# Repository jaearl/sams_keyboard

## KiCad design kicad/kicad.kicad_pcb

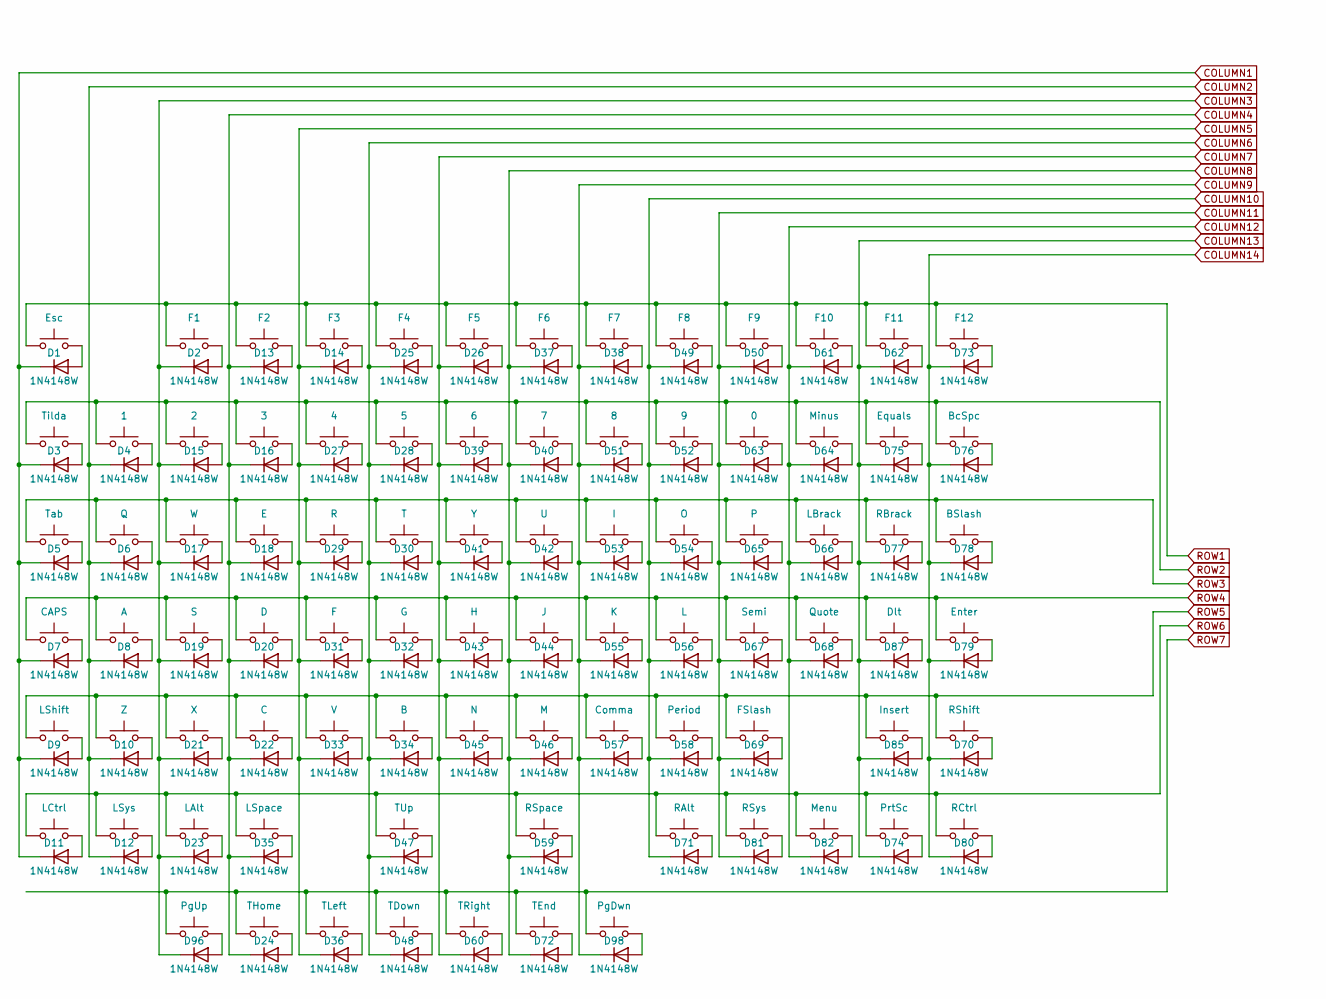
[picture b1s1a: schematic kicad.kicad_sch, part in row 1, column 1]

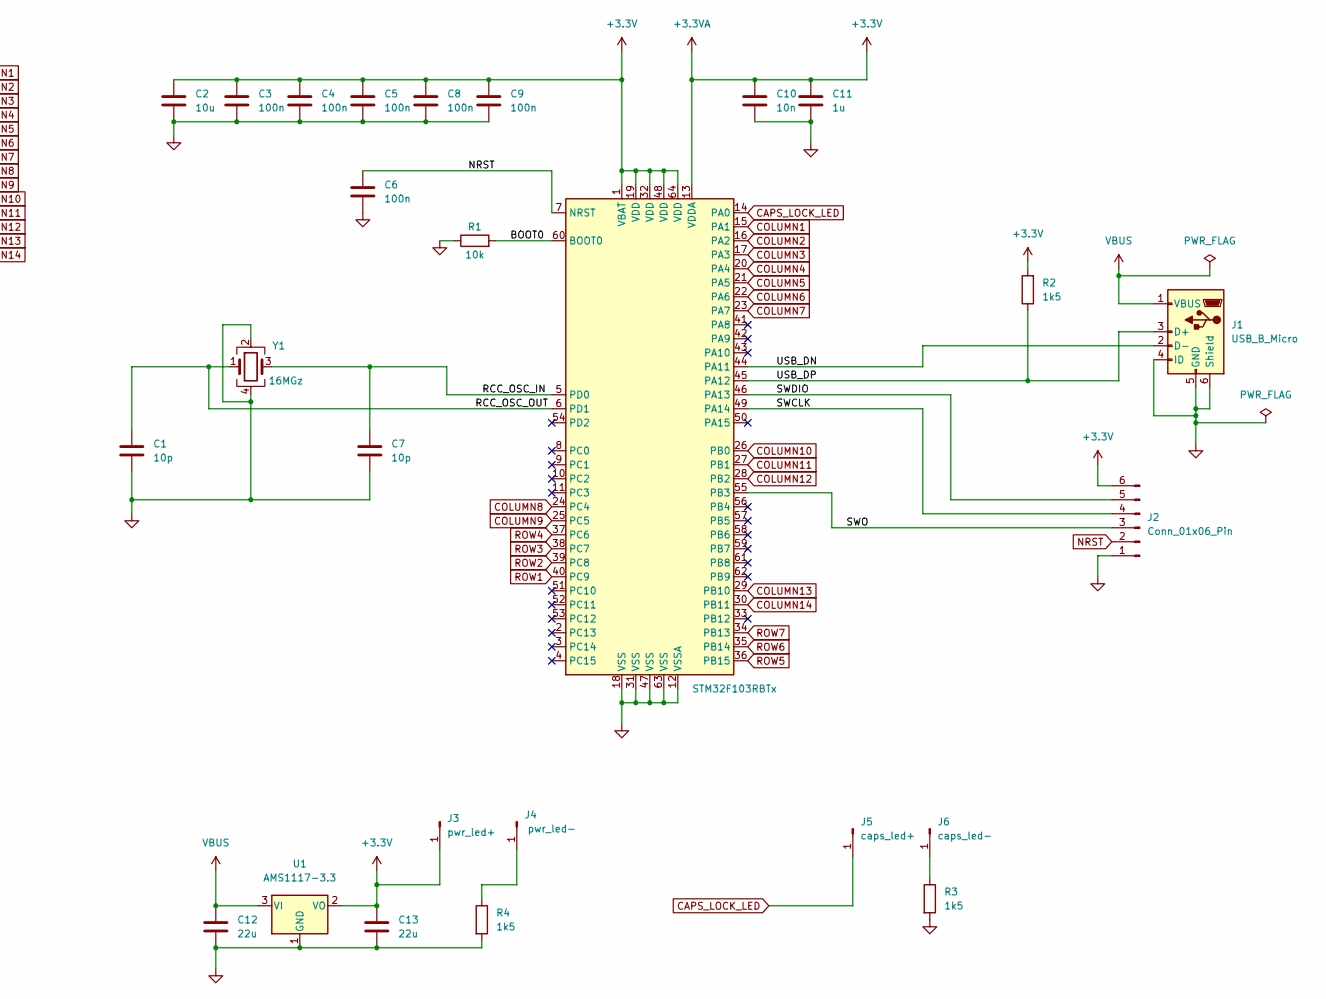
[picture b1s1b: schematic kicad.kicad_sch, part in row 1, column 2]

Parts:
C1, C7: 10p; C_0402_1005Metric
C2: 10u; C_0603_1608Metric
C3, C4, C5, C6, C8, C9: 100n; C_0402_1005Metric
C10: 10n; C_0402_1005Metric
C11: 1u; C_0402_1005Metric
C12, C13: 22u; C_0805_2012Metric
D1, D2, D3, D4, D5, D6, D7, D8, D9, D10, D11, D12, D13, D14, D15, D16, D17, D18, D19, D20, D21, D22, D23, D24, D25, D26, D27, D28, D29, D30, D31, D32, D33, D34, D35, D36, D37, D38, D39, D40, D41, D42, D43, D44, D45, D46, D47, D48, D49, D50, D51, D52, D53, D54, D55, D56, D57, D58, D59, D60, D61, D62, D63, D64, D65, D66, D67, D68, D69, D70, D71, D72, D73, D74, D75, D76, D77, D78, D79, D80, D81, D82, D85, D87, D96, D98: 1N4148W; D_SOD-123
J1: USB_B_Micro; USB_Micro-B_Wuerth_629105150521
J2: Conn_01x06_Pin
J3: pwr_led+; PinHeader_1x01_P2.54mm_Vertical
J4: pwr_led-; PinHeader_1x01_P2.54mm_Vertical
J5: caps_led+; PinHeader_1x01_P2.54mm_Vertical
J6: caps_led-; PinHeader_1x01_P2.54mm_Vertical
MCU1: STM32F103RBTx; LQFP-64_10x10mm_P0.5mm
R1: 10k; R_0402_1005Metric
R2: 1k5; R_0402_1005Metric
R3, R4: 1k5; R_0603_1608Metric
U1: AMS1117-3.3; SOT-223-3_TabPin2
Y1: 16MGz; Crystal_SMD_3225-4Pin_3.2x2.5mm
sw1: Esc; SW_Cherry_MX_1.00u_PCB
sw2: F1; SW_Cherry_MX_1.00u_PCB
sw3: Tilda; SW_Cherry_MX_1.00u_PCB
sw4: 1; SW_Cherry_MX_1.00u_PCB
sw5: Tab; SW_Cherry_MX_1.50u_PCB
sw6: Q; SW_Cherry_MX_1.00u_PCB
sw7: CAPS; SW_Cherry_MX_1.75u_PCB
sw8: A; SW_Cherry_MX_1.00u_PCB
sw9: LShift; SW_Cherry_MX_2.25u_PCB
sw10: Z; SW_Cherry_MX_1.00u_PCB
sw11: LCtrl; SW_Cherry_MX_1.25u_PCB
sw12: LSys; SW_Cherry_MX_1.25u_PCB
sw13: F2; SW_Cherry_MX_1.00u_PCB
sw14: F3; SW_Cherry_MX_1.00u_PCB
sw15: 2; SW_Cherry_MX_1.00u_PCB
sw16: 3; SW_Cherry_MX_1.00u_PCB
sw17: W; SW_Cherry_MX_1.00u_PCB
sw18: E; SW_Cherry_MX_1.00u_PCB
sw19: S; SW_Cherry_MX_1.00u_PCB
sw20: D; SW_Cherry_MX_1.00u_PCB
sw21: X; SW_Cherry_MX_1.00u_PCB
sw22: C; SW_Cherry_MX_1.00u_PCB
sw23: LAlt; SW_Cherry_MX_1.25u_PCB
sw24: THome; SW_Cherry_MX_1.00u_PCB
sw25: F4; SW_Cherry_MX_1.00u_PCB
sw26: F5; SW_Cherry_MX_1.00u_PCB
sw27: 4; SW_Cherry_MX_1.00u_PCB
sw28: 5; SW_Cherry_MX_1.00u_PCB
sw29: R; SW_Cherry_MX_1.00u_PCB
sw30: T; SW_Cherry_MX_1.00u_PCB
sw31: F; SW_Cherry_MX_1.00u_PCB
sw32: G; SW_Cherry_MX_1.00u_PCB
sw33: V; SW_Cherry_MX_1.00u_PCB
sw34: B; SW_Cherry_MX_1.00u_PCB
sw35: LSpace; SW_Cherry_MX_2.75u_PCB
sw36: TLeft; SW_Cherry_MX_1.00u_PCB
sw37: F6; SW_Cherry_MX_1.00u_PCB
sw38: F7; SW_Cherry_MX_1.00u_PCB
sw39: 6; SW_Cherry_MX_1.00u_PCB
sw40: 7; SW_Cherry_MX_1.00u_PCB
sw41: Y; SW_Cherry_MX_1.00u_PCB
sw42: U; SW_Cherry_MX_1.00u_PCB
sw43: H; SW_Cherry_MX_1.00u_PCB
sw44: J; SW_Cherry_MX_1.00u_PCB
sw45: N; SW_Cherry_MX_1.00u_PCB
sw46: M; SW_Cherry_MX_1.00u_PCB
sw47: TUp; SW_Cherry_MX_1.00u_PCB
sw48: TDown; SW_Cherry_MX_1.00u_PCB
sw49: F8; SW_Cherry_MX_1.00u_PCB
sw50: F9; SW_Cherry_MX_1.00u_PCB
sw51: 8; SW_Cherry_MX_1.00u_PCB
sw52: 9; SW_Cherry_MX_1.00u_PCB
sw53: I; SW_Cherry_MX_1.00u_PCB
sw54: O; SW_Cherry_MX_1.00u_PCB
sw55: K; SW_Cherry_MX_1.00u_PCB
sw56: L; SW_Cherry_MX_1.00u_PCB
sw57: Comma; SW_Cherry_MX_1.00u_PCB
sw58: Period; SW_Cherry_MX_1.00u_PCB
sw59: RSpace; SW_Cherry_MX_2.25u_PCB
sw60: TRight; SW_Cherry_MX_1.00u_PCB
sw61: F10; SW_Cherry_MX_1.00u_PCB
sw62: F11; SW_Cherry_MX_1.00u_PCB
sw63: 0; SW_Cherry_MX_1.00u_PCB
sw64: Minus; SW_Cherry_MX_1.00u_PCB
sw65: P; SW_Cherry_MX_1.00u_PCB
sw66: LBrack; SW_Cherry_MX_1.00u_PCB
sw67: Semi; SW_Cherry_MX_1.00u_PCB
sw68: Quote; SW_Cherry_MX_1.00u_PCB
sw69: FSlash; SW_Cherry_MX_1.00u_PCB
sw70: RShift; SW_Cherry_MX_2.75u_PCB
sw71: RAlt; SW_Cherry_MX_1.25u_PCB
sw72: TEnd; SW_Cherry_MX_1.00u_PCB
sw73: F12; SW_Cherry_MX_1.00u_PCB
sw74: PrtSc; SW_Cherry_MX_1.00u_PCB
sw75: Equals; SW_Cherry_MX_1.00u_PCB
sw76: BcSpc; SW_Cherry_MX_2.00u_PCB
sw77: RBrack; SW_Cherry_MX_1.00u_PCB
sw78: BSlash; SW_Cherry_MX_1.50u_PCB
sw79: Enter; SW_Cherry_MX_2.25u_PCB
sw80: RCtrl; SW_Cherry_MX_1.25u_PCB
sw81: RSys; SW_Cherry_MX_1.25u_PCB
sw82: Menu; SW_Cherry_MX_1.25u_PCB
sw85: Insert; SW_Cherry_MX_1.00u_PCB
sw87: Dlt; SW_Cherry_MX_1.00u_PCB
sw96: PgUp; SW_Cherry_MX_1.00u_PCB
sw98: PgDwn; SW_Cherry_MX_1.00u_PCB

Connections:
/BOOT0: MCU1.60 (BOOT0), R1.2
/RCC_OSC_IN: C7.1, MCU1.5 (PD0), Y1.3
/RCC_OSC_OUT: C1.1, MCU1.6 (PD1), Y1.1
/USB_DN: J1.2 (D-), MCU1.44 (PA11)
/USB_DP: J1.3 (D+), MCU1.45 (PA12), R2.1
CAPS_LOCK_LED: J5.1, MCU1.14 (PA0)
COLUMN1: D1.1 (K), D3.1 (K), D5.1 (K), D7.1 (K), D9.1 (K), D11.1 (K), MCU1.15 (PA1)
COLUMN2: D4.1 (K), D6.1 (K), D8.1 (K), D10.1 (K), D12.1 (K), MCU1.16 (PA2)
COLUMN3: D2.1 (K), D15.1 (K), D17.1 (K), D19.1 (K), D21.1 (K), D23.1 (K), D96.1 (K), MCU1.17 (PA3)
COLUMN4: D13.1 (K), D16.1 (K), D18.1 (K), D20.1 (K), D22.1 (K), D24.1 (K), D35.1 (K), MCU1.20 (PA4)
COLUMN5: D14.1 (K), D27.1 (K), D29.1 (K), D31.1 (K), D33.1 (K), D36.1 (K), MCU1.21 (PA5)
COLUMN6: D25.1 (K), D28.1 (K), D30.1 (K), D32.1 (K), D34.1 (K), D47.1 (K), D48.1 (K), MCU1.22 (PA6)
COLUMN7: D26.1 (K), D39.1 (K), D41.1 (K), D43.1 (K), D45.1 (K), D60.1 (K), MCU1.23 (PA7)
COLUMN8: D37.1 (K), D40.1 (K), D42.1 (K), D44.1 (K), D46.1 (K), D59.1 (K), D72.1 (K), MCU1.24 (PC4)
COLUMN9: D38.1 (K), D51.1 (K), D53.1 (K), D55.1 (K), D57.1 (K), D98.1 (K), MCU1.25 (PC5)
COLUMN10: D49.1 (K), D52.1 (K), D54.1 (K), D56.1 (K), D58.1 (K), D71.1 (K), MCU1.26 (PB0)
COLUMN11: D50.1 (K), D63.1 (K), D65.1 (K), D67.1 (K), D69.1 (K), D81.1 (K), MCU1.27 (PB1)
COLUMN12: D61.1 (K), D64.1 (K), D66.1 (K), D68.1 (K), D82.1 (K), MCU1.28 (PB2)
COLUMN13: D62.1 (K), D74.1 (K), D75.1 (K), D77.1 (K), D85.1 (K), D87.1 (K), MCU1.29 (PB10)
COLUMN14: D70.1 (K), D73.1 (K), D76.1 (K), D78.1 (K), D79.1 (K), D80.1 (K), MCU1.30 (PB11)
NRST: C6.1, MCU1.7 (NRST)
unnamed: D1.2 (A), sw1.2
unnamed: D2.2 (A), sw2.2
unnamed: D3.2 (A), sw3.2
unnamed: D4.2 (A), sw4.2
unnamed: D5.2 (A), sw5.2
unnamed: D6.2 (A), sw6.2
unnamed: D7.2 (A), sw7.2
unnamed: D8.2 (A), sw8.2
unnamed: D9.2 (A), sw9.2
unnamed: D10.2 (A), sw10.2
unnamed: D11.2 (A), sw11.2
unnamed: D12.2 (A), sw12.2
unnamed: D13.2 (A), sw13.2
unnamed: D14.2 (A), sw14.2
unnamed: D15.2 (A), sw15.2
unnamed: D16.2 (A), sw16.2
unnamed: D17.2 (A), sw17.2
unnamed: D18.2 (A), sw18.2
unnamed: D19.2 (A), sw19.2
unnamed: D20.2 (A), sw20.2
unnamed: D21.2 (A), sw21.2
unnamed: D22.2 (A), sw22.2
unnamed: D23.2 (A), sw23.2
unnamed: D24.2 (A), sw24.2
unnamed: D25.2 (A), sw25.2
unnamed: D26.2 (A), sw26.2
unnamed: D27.2 (A), sw27.2
unnamed: D28.2 (A), sw28.2
unnamed: D29.2 (A), sw29.2
unnamed: D30.2 (A), sw30.2
unnamed: D31.2 (A), sw31.2
unnamed: D32.2 (A), sw32.2
unnamed: D33.2 (A), sw33.2
unnamed: D34.2 (A), sw34.2
unnamed: D35.2 (A), sw35.2
unnamed: D36.2 (A), sw36.2
unnamed: D37.2 (A), sw37.2
unnamed: D38.2 (A), sw38.2
unnamed: D39.2 (A), sw39.2
unnamed: D40.2 (A), sw40.2
unnamed: D41.2 (A), sw41.2
unnamed: D42.2 (A), sw42.2
unnamed: D43.2 (A), sw43.2
unnamed: D44.2 (A), sw44.2
unnamed: D45.2 (A), sw45.2
unnamed: D46.2 (A), sw46.2
unnamed: D47.2 (A), sw47.2
unnamed: D48.2 (A), sw48.2
unnamed: D49.2 (A), sw49.2
unnamed: D50.2 (A), sw50.2
unnamed: D51.2 (A), sw51.2
unnamed: D52.2 (A), sw52.2
unnamed: D53.2 (A), sw53.2
unnamed: D54.2 (A), sw54.2
unnamed: D55.2 (A), sw55.2
unnamed: D56.2 (A), sw56.2
unnamed: D57.2 (A), sw57.2
unnamed: D58.2 (A), sw58.2
unnamed: D59.2 (A), sw59.2
unnamed: D60.2 (A), sw60.2
unnamed: D61.2 (A), sw61.2
unnamed: D62.2 (A), sw62.2
unnamed: D63.2 (A), sw63.2
unnamed: D64.2 (A), sw64.2
unnamed: D65.2 (A), sw65.2
unnamed: D66.2 (A), sw66.2
unnamed: D67.2 (A), sw67.2
unnamed: D68.2 (A), sw68.2
unnamed: D69.2 (A), sw69.2
unnamed: D70.2 (A), sw70.2
unnamed: D71.2 (A), sw71.2
unnamed: D72.2 (A), sw72.2
unnamed: D73.2 (A), sw73.2
unnamed: D74.2 (A), sw74.2
unnamed: D75.2 (A), sw75.2
unnamed: D76.2 (A), sw76.2
unnamed: D77.2 (A), sw77.2
unnamed: D78.2 (A), sw78.2
unnamed: D79.2 (A), sw79.2
unnamed: D80.2 (A), sw80.2
unnamed: D81.2 (A), sw81.2
unnamed: D82.2 (A), sw82.2
unnamed: D85.2 (A), sw85.2
unnamed: D87.2 (A), sw87.2
unnamed: D96.2 (A), sw96.2
unnamed: D98.2 (A), sw98.2
unnamed: J4.1, R4.1
unnamed: J6.1, R3.1
ROW1: MCU1.40 (PC9), sw1.1, sw2.1, sw13.1, sw14.1, sw25.1, sw26.1, sw37.1, sw38.1, sw49.1, sw50.1, sw61.1, sw62.1, sw73.1
ROW2: MCU1.39 (PC8), sw3.1, sw4.1, sw15.1, sw16.1, sw27.1, sw28.1, sw39.1, sw40.1, sw51.1, sw52.1, sw63.1, sw64.1, sw75.1, sw76.1
ROW3: MCU1.38 (PC7), sw5.1, sw6.1, sw17.1, sw18.1, sw29.1, sw30.1, sw41.1, sw42.1, sw53.1, sw54.1, sw65.1, sw66.1, sw77.1, sw78.1
ROW4: MCU1.37 (PC6), sw7.1, sw8.1, sw19.1, sw20.1, sw31.1, sw32.1, sw43.1, sw44.1, sw55.1, sw56.1, sw67.1, sw68.1, sw79.1, sw87.1
ROW5: MCU1.36 (PB15), sw9.1, sw10.1, sw21.1, sw22.1, sw33.1, sw34.1, sw45.1, sw46.1, sw57.1, sw58.1, sw69.1, sw70.1, sw85.1
ROW6: MCU1.35 (PB14), sw11.1, sw12.1, sw23.1, sw35.1, sw47.1, sw59.1, sw71.1, sw74.1, sw80.1, sw81.1, sw82.1
ROW7: MCU1.34 (PB13), sw24.1, sw36.1, sw48.1, sw60.1, sw72.1, sw96.1, sw98.1
VBUS: C12.1, J1.1 (VBUS), U1.3 (VI)

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
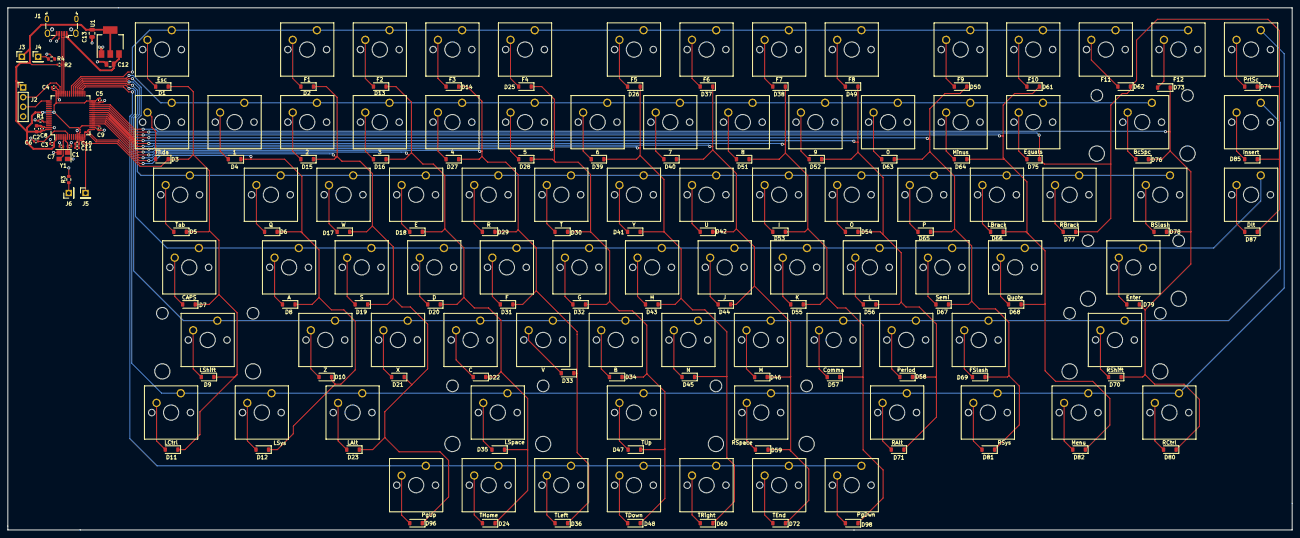
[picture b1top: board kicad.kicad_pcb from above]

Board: 2 copper layers, 337.0 x 137.0 mm, 198 parts (0 on the bottom side), 121 nets.

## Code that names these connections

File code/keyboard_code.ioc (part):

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Mcu.Name=STM32F103R(8-B)Tx
Mcu.Package=LQFP64
Mcu.UserName=STM32F103RBTx
PA0-WKUP.GPIOParameters=GPIO_PuPd,GPIO_Label
PA0-WKUP.GPIO_Label=COLUMN10
PA0-WKUP.GPIO_PuPd=GPIO_PULLDOWN
PA0-WKUP.Signal=GPIO_Input
PA13.Mode=Trace_Asynchronous_SW
PA13.Signal=SYS_JTMS-SWDIO
PA14.Mode=Trace_Asynchronous_SW
PA14.Signal=SYS_JTCK-SWCLK
PA6.GPIOParameters=GPIO_Speed,PinState,GPIO_PuPd,GPIO_Label
PA6.GPIO_Label=ROW7
PA6.GPIO_PuPd=GPIO_PULLDOWN
PA6.GPIO_Speed=GPIO_SPEED_FREQ_HIGH
PA6.PinState=GPIO_PIN_SET
PA6.Signal=GPIO_Output
PB0.GPIOParameters=GPIO_Speed,PinState,GPIO_PuPd,GPIO_Label,GPIO_ModeDefaultOutputPP
PB0.GPIO_Label=CAPS_LOCK
PB0.GPIO_ModeDefaultOutputPP=GPIO_MODE_OUTPUT_PP
PB0.GPIO_PuPd=GPIO_PULLDOWN
PB0.GPIO_Speed=GPIO_SPEED_FREQ_HIGH
PB0.PinState=GPIO_PIN_SET
PB0.Signal=GPIO_Output
PB3.Mode=Trace_Asynchronous_SW
PB3.Signal=SYS_JTDO-TRACESWO
PC5.GPIOParameters=GPIO_PuPd,GPIO_Label
PC5.GPIO_Label=COLUMN9
PC5.GPIO_PuPd=GPIO_PULLDOWN
PC5.Signal=GPIO_Input
PC9.GPIOParameters=PinState,GPIO_PuPd,GPIO_Label,GPIO_ModeDefaultOutputPP
PC9.GPIO_Label=ROW1
PC9.GPIO_ModeDefaultOutputPP=GPIO_MODE_OUTPUT_PP
PC9.GPIO_PuPd=GPIO_PULLDOWN
PC9.PinState=GPIO_PIN_SET
PC9.Signal=GPIO_Output
RCC.SYSCLKFreq_VALUE=8000000
RCC.SYSCLKSource=RCC_SYSCLKSOURCE_PLLCLK
board=custom

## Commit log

2023-02-04 crap
2023-02-04 startup pcb
2023-02-06 Add decoupling circuits
2023-02-06 fix decoupling for VDDA to just follow recommendations
2023-02-06 Add basic voltage regulator
2023-02-12 Ground NRST and BOOT0. Delete old auto generated backup files. Don't use 'git add .' when committing...
2023-02-14 Add swd debug, finish usb
2023-02-16 Connect matrix to gpio lines
2023-02-17 Add caps lock led
2023-02-25 gitignore autobackups
2023-02-25 add plugin we used
2023-02-25 route rows
2023-03-06 finish basic oscillator circuitry
2023-03-07 route columns
2023-03-07 working towards merge
2023-03-07 recover small change lost in merge
2023-03-07 Passing electrical rules check
2023-03-10 Adjustments for new selected crystal part
2023-03-11 All footprints selected, all parts sourced
2023-04-02 component rough layout
2023-04-22 getting close to pcb first draft
2023-04-23 Some cleanup
2023-04-23 Setup edges, starting DRC fixes
2023-04-25 Passing DRC
2023-04-28 Get rid of need for key signals on left side of board
2023-04-28 little more trace cleanup
2023-05-01 layout new diodes
2023-05-02 correct RShift footprint
2023-05-02 fix traces getting clobbered by new holes
2023-05-13 fix DRC warnings from moving to kicad 7
2023-05-14 move diodes
2023-05-14 add vias, passing DRC. PCB now 1-sided yay
2023-05-14 Some touch ups and fix the 3d model for the connector
2023-05-16 square board
2023-05-18 Change thickness of pcb and usb diff pair
2023-05-28 latest
2023-05-29 add keyboard code
2023-05-30 Get swd and swv working on nucleo
2023-05-31 75% layout
2023-05-31 update gitignore for kicad
2023-05-31 75% layout pcb
2023-05-31 change line endings
2023-05-31 connect grid to mcu
